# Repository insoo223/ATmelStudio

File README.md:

# ATmelStudio
AVR C codes developed by ATmel Studio 7.0

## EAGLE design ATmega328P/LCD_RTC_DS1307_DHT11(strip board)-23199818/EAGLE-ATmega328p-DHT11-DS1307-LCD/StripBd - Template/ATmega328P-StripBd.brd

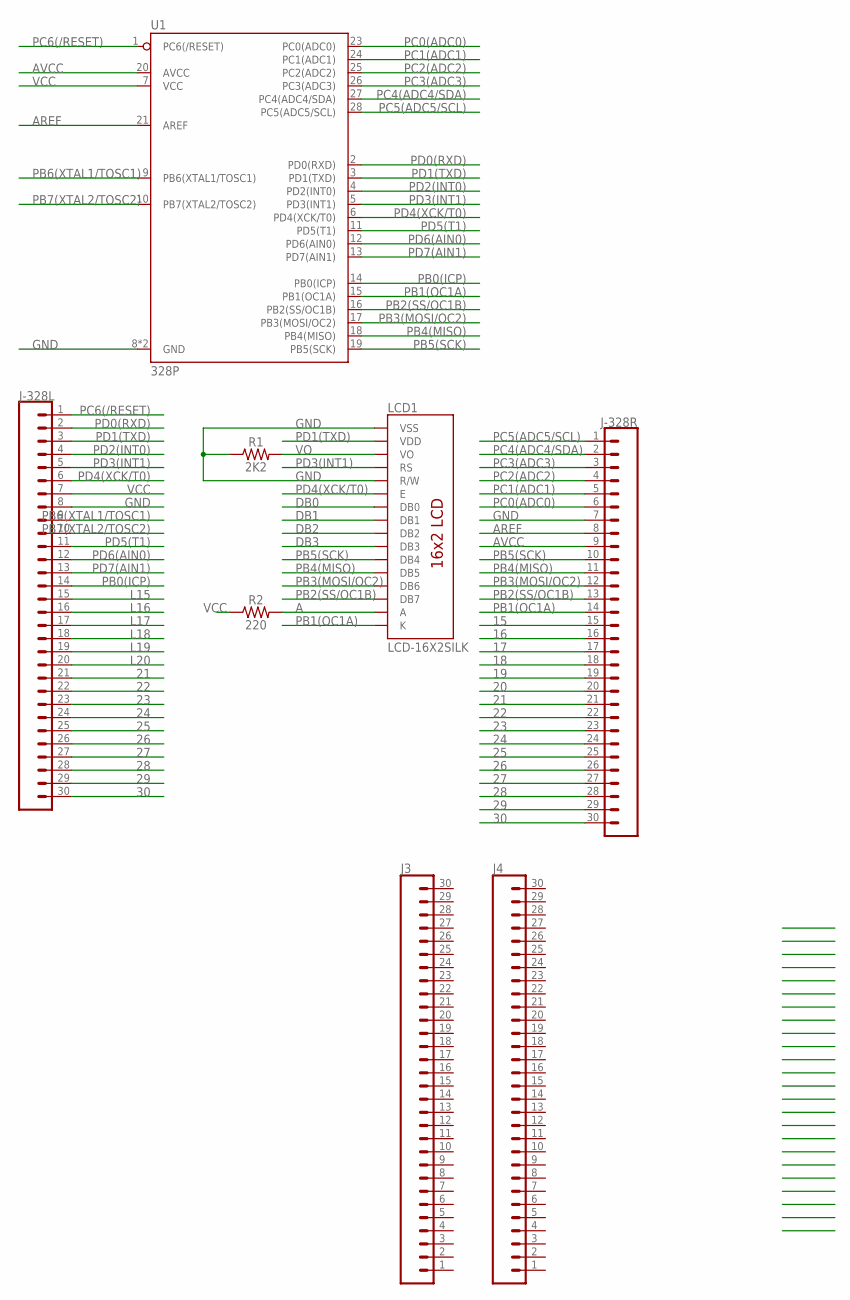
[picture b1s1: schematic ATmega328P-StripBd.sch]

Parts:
J3, J4: CONN_30; 1X30
J-328L, J-328R: CONN_30; 1X30
LCD1: LCD-16X2SILK; LCD-16X2
R1: 2K2; AXIAL-0.3
R2: 220; AXIAL-0.3
U1: 328P; DIP28

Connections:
15: J-328R.15
16: J-328R.16
17: J-328R.17
18: J-328R.18
19: J-328R.19
20: J-328R.20
21: J-328L.21, J-328R.21
22: J-328L.22, J-328R.22
23: J-328L.23, J-328R.23
24: J-328L.24, J-328R.24
25: J-328L.25, J-328R.25
26: J-328L.26, J-328R.26
27: J-328L.27, J-328R.27
28: J-328L.28, J-328R.28
29: J-328L.29, J-328R.29
30: J-328L.30, J-328R.30
A: LCD1.15 (A), R2.P$2 (2)
AREF: J-328R.8, U1.21 (AREF)
AVCC: J-328R.9, U1.20 (AVCC)
DB0: LCD1.7 (DB0)
DB1: LCD1.8 (DB1)
DB2: LCD1.9 (DB2)
DB3: LCD1.10 (DB3)
GND: J-328L.8, J-328R.7, LCD1.1 (VSS), LCD1.5 (R/W), R1.P$1 (1), U1.8 (GND), U1.22 (GND)
L15: J-328L.15
L16: J-328L.16
L17: J-328L.17
L18: J-328L.18
L19: J-328L.19
L20: J-328L.20
PB0(ICP): J-328L.14, U1.14 (PB0(ICP))
PB1(OC1A): J-328R.14, LCD1.16 (K), U1.15 (PB1(OC1A))
PB2(SS/OC1B): J-328R.13, LCD1.14 (DB7), U1.16 (PB2(SS/OC1B))
PB3(MOSI/OC2): J-328R.12, LCD1.13 (DB6), U1.17 (PB3(MOSI/OC2))
PB4(MISO): J-328R.11, LCD1.12 (DB5), U1.18 (PB4(MISO))
PB5(SCK): J-328R.10, LCD1.11 (DB4), U1.19 (PB5(SCK))
PB6(XTAL1/TOSC1): J-328L.9, U1.9 (PB6(XTAL1/TOSC1))
PB7(XTAL2/TOSC2): J-328L.10, U1.10 (PB7(XTAL2/TOSC2))
PC0(ADC0): J-328R.6, U1.23 (PC0(ADC0))
PC1(ADC1): J-328R.5, U1.24 (PC1(ADC1))
PC2(ADC2): J-328R.4, U1.25 (PC2(ADC2))
PC3(ADC3): J-328R.3, U1.26 (PC3(ADC3))
PC4(ADC4/SDA): J-328R.2, U1.27 (PC4(ADC4/SDA))
PC5(ADC5/SCL): J-328R.1, U1.28 (PC5(ADC5/SCL))
PC6(/RESET): J-328L.1, U1.1 (PC6(/RESET))
PD0(RXD): J-328L.2, U1.2 (PD0(RXD))
PD1(TXD): J-328L.3, LCD1.2 (VDD), U1.3 (PD1(TXD))
PD2(INT0): J-328L.4, U1.4 (PD2(INT0))
PD3(INT1): J-328L.5, LCD1.4 (RS), U1.5 (PD3(INT1))
PD4(XCK/T0): J-328L.6, LCD1.6 (E), U1.6 (PD4(XCK/T0))
PD5(T1): J-328L.11, U1.11 (PD5(T1))
PD6(AIN0): J-328L.12, U1.12 (PD6(AIN0))
PD7(AIN1): J-328L.13, U1.13 (PD7(AIN1))
VCC: J-328L.7, R2.P$1 (1), U1.7 (VCC)
VO: LCD1.3 (VO), R1.P$2 (2)

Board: 2 copper layers, 8 parts (0 on the bottom side), 39 nets, no tracks yet.

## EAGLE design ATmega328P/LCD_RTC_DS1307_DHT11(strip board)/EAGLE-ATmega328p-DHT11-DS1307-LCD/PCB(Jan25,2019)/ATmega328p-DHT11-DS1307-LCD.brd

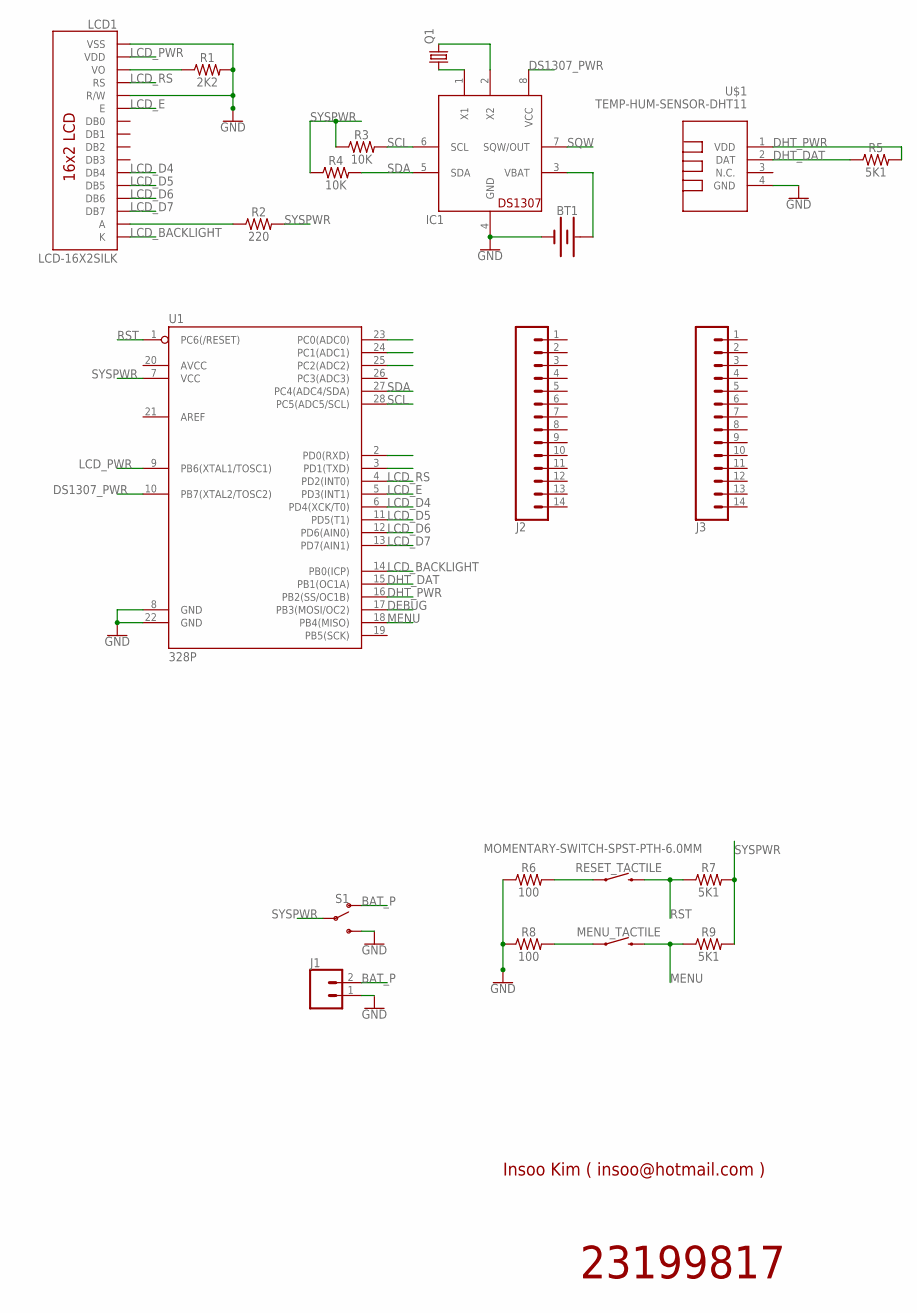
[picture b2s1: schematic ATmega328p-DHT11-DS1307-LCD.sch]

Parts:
BT1: BATTERY-20MM_PTH; BATTCOM_20MM_PTH
IC1: DS1307; DIL08
J1: CONN_02; 1X02
J2, J3: CONN_14; 1X14
LCD1: LCD-16X2SILK; LCD-16X2
MENU_TACTILE: MOMENTARY-SWITCH-SPST-PTH-6.0MM; TACTILE_SWITCH_PTH_6.0MM
Q1: CRYSTALTC26H; TC26H
R1: 2K2; AXIAL-0.3
R2: 220; AXIAL-0.3
R3, R4: 10K; AXIAL-0.3
R5, R7, R9: 5K1; AXIAL-0.3
R6, R8: 100; AXIAL-0.3
RESET_TACTILE: MOMENTARY-SWITCH-SPST-PTH-6.0MM; TACTILE_SWITCH_PTH_6.0MM
S1: SWITCH-SPDT-PTH-11.6X4.0MM; SWITCH_SPDT_PTH_11.6X4.0MM
U1: 328P; DIP28
U$1: TEMP-HUM-SENSOR-DHT11

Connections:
BAT_P: J1.2, S1.1 (O)
DEBUG: U1.17 (PB3(MOSI/OC2))
DHT_DAT: R5.P$1 (1), U1.15 (PB1(OC1A)), U$1.2 (DAT)
DHT_PWR: R5.P$2 (2), U1.16 (PB2(SS/OC1B)), U$1.1 (VDD)
DS1307_PWR: IC1.8 (VCC), U1.10 (PB7(XTAL2/TOSC2))
GND: BT1.2 (-), IC1.4 (GND), J1.1, LCD1.1 (VSS), LCD1.5 (R/W), R1.P$2 (2), R6.P$1 (1), R8.P$1 (1), S1.3 (S), U1.8 (GND), U1.22 (GND), U$1.4 (GND)
LCD_BACKLIGHT: LCD1.16 (K), U1.14 (PB0(ICP))
LCD_D4: LCD1.11 (DB4), U1.6 (PD4(XCK/T0))
LCD_D5: LCD1.12 (DB5), U1.11 (PD5(T1))
LCD_D6: LCD1.13 (DB6), U1.12 (PD6(AIN0))
LCD_D7: LCD1.14 (DB7), U1.13 (PD7(AIN1))
LCD_E: LCD1.6 (E), U1.5 (PD3(INT1))
LCD_PWR: LCD1.2 (VDD), U1.9 (PB6(XTAL1/TOSC1))
LCD_RS: LCD1.4 (RS), U1.4 (PD2(INT0))
MENU: MENU_TACTILE.3 (2), R9.P$1 (1), U1.18 (PB4(MISO))
unnamed: MENU_TACTILE.1, R8.P$2 (2)
unnamed: BT1.1 (+), IC1.3 (VBAT)
unnamed: LCD1.3 (VO), R1.P$1 (1)
unnamed: R6.P$2 (2), RESET_TACTILE.1
unnamed: IC1.1 (X1), Q1.1
unnamed: IC1.2 (X2), Q1.2
unnamed: LCD1.15 (A), R2.P$1 (1)
RST: R7.P$1 (1), RESET_TACTILE.3 (2), U1.1 (PC6(/RESET))
SCL: IC1.6 (SCL), R3.P$2 (2), U1.28 (PC5(ADC5/SCL))
SDA: IC1.5 (SDA), R4.P$2 (2), U1.27 (PC4(ADC4/SDA))
SQW: IC1.7 (SQW/OUT)
SYSPWR: R2.P$2 (2), R3.P$1 (1), R4.P$1 (1), R7.P$2 (2), R9.P$2 (2), S1.2, U1.7 (VCC)

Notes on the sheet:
23199817
Insoo Kim ( insoo@hotmail.com )

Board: 2 copper layers, 21 parts (0 on the bottom side), 25 nets, no tracks yet.

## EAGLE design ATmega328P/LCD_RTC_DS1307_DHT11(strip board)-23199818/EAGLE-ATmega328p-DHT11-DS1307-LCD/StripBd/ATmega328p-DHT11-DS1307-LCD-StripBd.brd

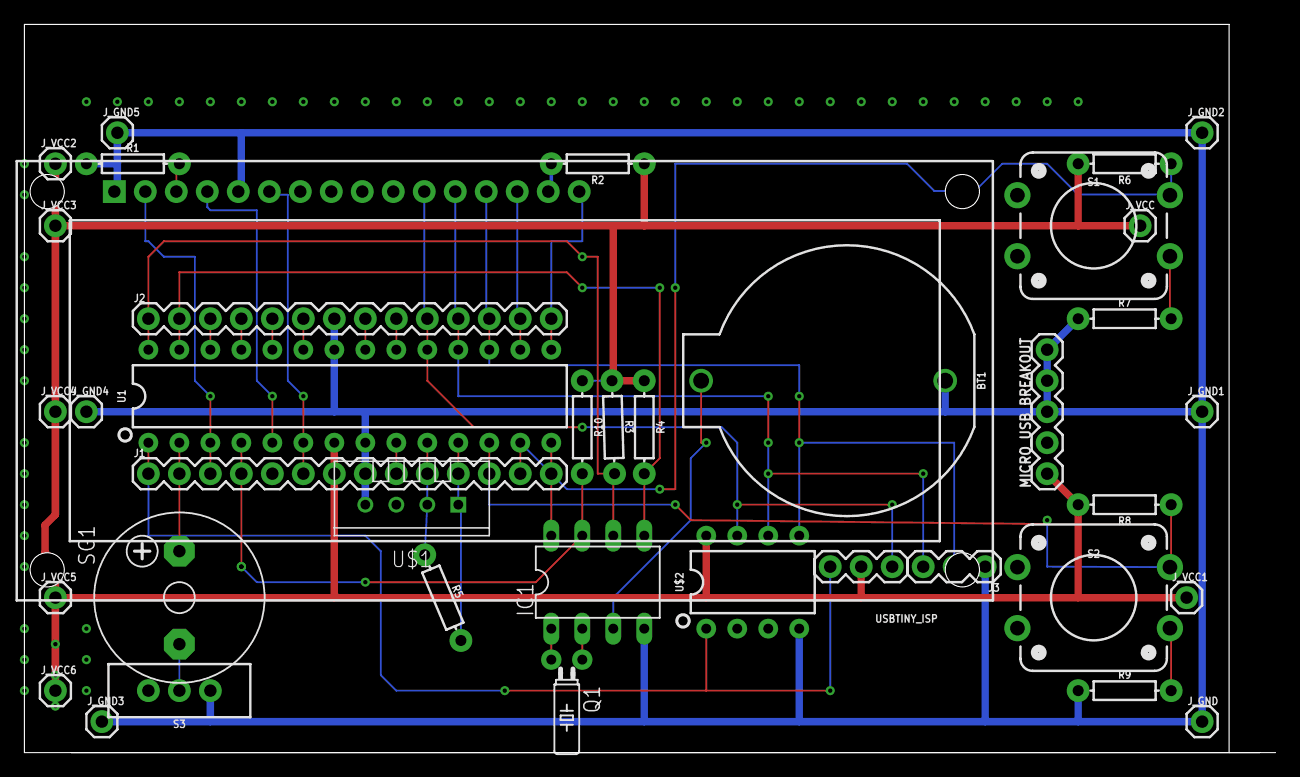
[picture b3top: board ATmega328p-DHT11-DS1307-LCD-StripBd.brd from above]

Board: 2 copper layers, 102.5 x 59.7 mm, 39 parts (0 on the bottom side), 35 nets.

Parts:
BT1: BATTCOM_20MM_PTH
IC1: DS1307; DIL08
J1, J2: 1X14
J3: 455-1750-1-ND; 1X03
J_GND, J_GND1, J_GND2, J_GND3, J_GND4, J_GND5: 1X01
J_VCC, J_VCC1, J_VCC2, J_VCC3, J_VCC4, J_VCC5, J_VCC6: 1X01
LCD1: LCD-16X2SILK; LCD-16X2
MICRO_USB_BREAKOUT: 1X05
Q1: TC26H
R1: 2K2; AXIAL-0.3
R2: 220; AXIAL-0.3
R3, R4, R10: 10K; AXIAL-0.3
R5, R6, R8: 5K1; AXIAL-0.3
R7, R9: 100; AXIAL-0.3
S1, S2: MOMENTARY-SWITCH-SPST-PTH-12MM; TACTILE_SWITCH_PTH_12MM
S3: SWITCH_SPDT_PTH_11.6X4.0MM
SG1: F/CM12P
U1: 328P; DIP28
U$1: TEMP-HUM-SENSOR-DHT11
U$2: ATTINY13DIP; DIP08_MCU
USBTINY_ISP: 455-1750-1-ND; 1X03

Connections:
A: LCD1.15, R2.P$2
AREF: J2.8, U1.21
AVCC: J2.9, U1.20
GND: BT1.2, IC1.4, J1.8, J2.7, J3.1, J_GND.1, J_GND1.1, J_GND2.1, J_GND3.1, J_GND4.1, J_GND5.1, LCD1.1, LCD1.5, MICRO_USB_BREAKOUT.5, R1.P$1, R7.P$1, R9.P$1, S3.3, U1.8, U1.22, U$1.4, U$2.4
unnamed: S3.2, SG1.-
unnamed: R7.P$2, S1.1
unnamed: IC1.2, Q1.1
unnamed: IC1.1, Q1.2
unnamed: R9.P$2, S2.1
unnamed: BT1.1, IC1.3
PB0(ICP): IC1.8, J1.14, U1.14
PB1(OC1A): J2.14, LCD1.16, U1.15
PB2(SS/OC1B): J2.13, LCD1.14, U1.16
PB3(MOSI/OC2)PB0(TINY8): J2.12, J3.2, LCD1.13, U1.17, U$2.5
PB4(MISO)PB1(TINY8): J2.11, J3.3, LCD1.12, U1.18, U$2.6
PB5(SCK)PB2(TINY8): J2.10, LCD1.11, U1.19, U$2.7, USBTINY_ISP.1
PB6(XTAL1/TOSC1): J1.9, U1.9
PB7(XTAL2/TOSC2): J1.10, R5.P$1, U1.10, U$1.2
PC0(ADC0): J2.6, U1.23
PC1(ADC1): J2.5, U1.24
PC2(ADC2): J2.4, U1.25
PC3(ADC3): J2.3, U1.26
PC4(ADC4/SDA): IC1.5, J2.2, R4.P$2, U1.27
PC5(ADC5/SCL): IC1.6, J2.1, R3.P$2, U1.28
PC6(/RESET)PB5(TINY8): J1.1, U1.1, U$2.1, USBTINY_ISP.3
PD0(RXD): J1.2, SG1.+, U1.2
PD1(TXD): J1.3, LCD1.2, U1.3
PD2(INT0): IC1.7, J1.4, R10.P$2, U1.4
PD3(INT1): J1.5, LCD1.4, U1.5
PD4(XCK/T0): J1.6, LCD1.6, U1.6
PD5(T1): J1.11, R5.P$2, U1.11, U$1.1
PD6(AIN0): J1.12, R8.P$1, S2.3, U1.12
PD7(AIN1): J1.13, R6.P$1, S1.3, U1.13
VCC: J1.7, J_VCC.1, J_VCC1.1, J_VCC2.1, J_VCC3.1, J_VCC4.1, J_VCC5.1, J_VCC6.1, MICRO_USB_BREAKOUT.1, R2.P$1, R3.P$1, R4.P$1, R6.P$2, R8.P$2, R10.P$1, U1.7, U$2.8, USBTINY_ISP.2
VO: LCD1.3, R1.P$2

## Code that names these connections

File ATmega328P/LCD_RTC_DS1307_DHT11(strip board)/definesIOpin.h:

/*
 * definesIOpin.h
 *
 Created: 2017-07-16 오전 10:55:47
 
 Author: insoo Kim (insoo@hotmail.com)
 
 Updated :
	Jan 28, 2019: Pin re-assigned for strip board implementation. Wired based on pins vicinity.

 */ 


#ifndef definesIOpin_H_
#define definesIOpin_H_

/**** MCU PIN assignment *******************
datasheet: Ch.
***********************************/

/*--- strip board PIN ASSIGNMENTS since Jan 28, 2019

ATmega328p	LCD		DS1307		DHT11	TACTILE_SW	BUZZER
PB0					VCC
PB1			K
PB2			D7
PB3			D6
PB4			D5
PB5			D4
PB6
PB7								DAT(SIG)

PD0													BUZ_PLUS
PD1			VDD
PD2					SQW
PD3			RS
PD4			E
PD5								VCC
PD6										SW1
PD7										SW2

PC0
PC1
PC2
PC3
PC4
PC5
PC6
--------------------------------------------------------*/

//------ LCD (Character 2 by 8) pin assignments 
// LCD interface (should agree with the diagram in LCD.c)
// make sure that the LCD RW pin is connected to GND

//added by Insoo (Jul 11, 2017)
#define lcd_VDD_port     PORTD      // lcd Vdd (Power supply) pin
#define lcd_VDD_bit      PORTD1 // From PORTB6 updated on Jan 28, 2019
#define lcd_VDD_ddr      DDRD

#define lcd_RS_port     PORTD       // lcd Register Select pin
#define lcd_RS_bit      PORTD3 // From 2 updated on Jan 28, 2019
#define lcd_RS_ddr      DDRD

#define lcd_E_port      PORTD                   // lcd Enable pin
#define lcd_E_bit       PORTD4 // From 3 updated on Jan 28, 2019
#define lcd_E_ddr       DDRD

#define lcd_D4_port     PORTB                   // lcd D4 connection
#define lcd_D4_bit      PORTB5 // From PORTD4 updated on Jan 28, 2019
#define lcd_D4_ddr      DDRB

#define lcd_D5_port     PORTB                   // lcd D5 connection
#define lcd_D5_bit      PORTB4 // From PORTD5 updated on Jan 28, 2019
#define lcd_D5_ddr      DDRB

#define lcd_D6_port     PORTB                   // lcd D6 connection
#define lcd_D6_bit      PORTB3 // From PORTD6 updated on Jan 28, 2019
#define lcd_D6_ddr      DDRB

#define lcd_D7_port     PORTB                   // lcd D7 connection
#define lcd_D7_bit      PORTB2 // From PORTD7 updated on Jan 28, 2019
#define lcd_D7_ddr      DDRB

#define lcd_Backlight_port PORTB
#define lcd_Backlight_bit  PORTB1 // From PORTB0 updated on Jan 28, 2019
									// LCD K pin, active low
#define lcd_Backlight_ddr  DDRB


//------ DS1307 Real-Time clock chip pin assignments
//added by Insoo (Jul 12, 2017)
#define DS1307_VCC_port     PORTB   // DS1307 VCC (Power supply) pin
#define DS1307_VCC_bit      PORTB0  // From PORTB7 updated on Jan 28, 2019
#define DS1307_VCC_ddr      DDRB

//added by Insoo (Jan 28, 2019)
#define DS1307_SQW_port     PIND   // DS1307 SQW (Square Wave or Control) pin
#define DS1307_SQW_bit      PORTD2  
#define DS1307_SQW_ddr      DDRD

//------ DHT11 digital temperature & humidity sensor pin assignments
//added by Insoo (Jul 14, 2017)
#define DHT_VCC_port     PORTD
#define DHT_VCC_bit      PORTD5  // From PORTB2 updated on Jan 28, 2019
#define DHT_VCC_ddr      DDRD

//naming conformity by Insoo (Jul 16, 2017)
#define DHT_SIG_port     PORTB
#define DHT_SIG_bit		 PORTB7 // From PORTB1 updated on Jan 28, 2019
#define DHT_SIG_ddr      DDRB

//------ Switches pin assignments
#define tactile_Switch_port PIND // input pin
#define tactile_Switch_bit  PORTD6  // From PORTB4 updated on Jan 28, 2019
#define tactile_Switch_ddr  DDRD

//added by Insoo (Jan 28, 2019)
#define tactile_Switch2_port PIND
#define tactile_Switch2_bit  PORTD7  
#define tactile_Switch2_ddr  DDRD

//------ Buzzer pin assignments
//added by Insoo (Jan 28, 2019)
#define BUZZER_port      PORTD
#define BUZZER_bit       PORTD0
#define BUZZER_ddr       DDRD

//added by Insoo (Jul 14, 2017)
#define debug_PIN_port     PORTB      // debug pin
#define debug_PIN_bit      PORTB6	// From 3 updated on Jan 28, 2019
#define debug_PIN_ddr      DDRB

#endif /* definesIOpin_H_ */

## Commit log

2017-07-14 Update README.md
    add AS version
2017-07-14 Create main.c
    LCD응용 프로그램 메인
2017-07-15 로컬PC에서 코드 업로드
    로컬PC에서 작업하던 ATmega328P LCD응용 소스코드를 깃허브에 화일 업로드
2017-07-15 setTime2DS1307() 추가
    DS1307시간설정 함수화
2017-07-15 Work & Sleep 0.2 uA 초절전 모드 실현!
    LCD 데이터 핀 네개와 Enable핀에 대해서 turn off 한 후, 핀을 input mode로 바꿀 때 비로소 엄청난 잠을 자게 된다. 동작 후 잠자는 동안 전류는 고작 0.2 micro ampere 즉 200 nano ampere 뿐!
2017-07-15 SetTimeDate함수에 입력변수 추가
    void SetTimeDate()에서
    void SetTimeDate(byte wkDay,byte month,byte day,byte year, byte ampm, byte h, byte m, byte s)
2017-07-15 전력절감 실험 동영상
    유튜브 게시
2017-07-16 Explicit defines
    Define header files are separated to make them more easily manageable.
2017-07-16 LCD, DS1307 function clarification
    More structure on codes
2017-07-16 More trimming codes i.e.Power Save
    Still aligning code file structure
2017-07-16 initISR test branch
    set a new branch to test interrupt service routines.
2017-07-16 compile err
    after separating definitions, got err but not yet resolved
2017-07-16 Add ignore files
    compiler outputs are ignored by Git
2017-07-16 ignor elf, hex, lss
2017-07-16 ignore
2017-07-16 trivial update to test .gitignore
2017-07-16 trivial
2017-07-16 Give externs.h more structure
    sort out extern function prototypes
2017-07-16 structured externs recovered from odd git
2017-07-16 confirm pushed testISR works fine
    some odd git operation has been resolved and confirmed it works fine on local machine.
2017-07-16 Renew master branch with successfully confirmed testISR branch
    For automatic merget or pull request seems not work, so that get the job done manually.
2017-07-16 add Makefile
2017-07-16 update .gitignore
    add Makefile via Git Desktop
2017-07-16 eeprom test w/DHT11
2017-07-18 add EEPROM.c , Eagle CAD schematic folder
2017-07-18 Vo w/2K2 and GND not to Vcc
    Vo(Contrast of LCD) connection to Vcc has been modified to GND.
2017-07-18 Sites of pinout map
    Box.com and references
2017-07-18 add site of datasheet
2017-07-18 add Coding Music of Bach
    Good to concentrate and pop up creative perspectives.
2017-07-18 EWR_ds1307 success
    Success on EEPROM write & read w/DS1307 RTC hour, minutes and second.
2017-07-19 eeprom ds1307 depends on ambient temp!
    When the sun rises, the result seems non-deterministic.
2018-11-17 Add ATtiny13A projects
    add from box.com
2018-11-17 directory re-arrangement
2018-11-17 directory rearrangement
2019-02-11 updated after pausing a while
    스마트 팜에 적용할 아이디어 시험용.
2019-02-13 ds1307 current time updated
2019-02-13 test success at E5200 PC
2019-05-19 changed
2019-08-04 DS1307 RTC chip power save
    In function "RTC_DS1307config", set DS1307 RTC chip power turn on to save coin cell battery
    DS1307_VCC_port |= _BV(DS1307_VCC_bit);
2019-08-04 PN Update
2019-08-05 Summer Fan Ctrl
    Add saftey-off feature after two-hour long operation
2019-08-07 Safety Stop after two hours of operation
2019-08-07 Safety off after 2hours of operation
2019-08-07 Slide switches for operation mode setting
2019-08-10 Chk on LG, but Not Working
2019-08-11 Update to manage conflict
2019-08-11 Update by 서재조립PC
2019-08-11 Update by 인수서재조립PC
2019-08-11 Update by 서재 LG
2019-08-11 Update by LGpc
2019-09-15 update binary
2019-10-19 check for working
2019-10-19 checking for working at EG-31M
2020-01-04 Check still working
2020-03-22 On for 60min, off for 30m
    Update ISR
2020-03-22 Uneven timer on & off
2020-08-22 Adjust Turn-on Threshold
    Bathroom LED bulb should Turn On even in the brightness of when the kitchen light is on
2020-08-22 RF315Mhz Remote to control summer fan
    Using ATtiny13A on Insoo's DIY board
2020-08-22 3 switches perf b'd multi-timer (1-2-3 min for left-mid-rite switch)
2020-10-04 Turn on threshold 160 to 200
2020-11-08 Remove directory containing long file name and not required to maintain
2021-10-23 new & old WDTsetup functions are shown in the code.
2021-10-23 added read switch ft. readSW()
2021-10-23 add ft. closing comment to readSW()
2021-11-14 update words & menu
2021-11-15 build on InsooDesk at TIM

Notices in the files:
parts and their libraries:
SparkFun-IC-Microcontroller: Licensing: Creative Commons ShareAlike 4.0 International - https://creativecommons.org/licenses/by-sa/4.0
diy-modules: Released under the Creative Commons Attribution 4.0 International License: http://creativecommons.org/licenses/by/4.0
